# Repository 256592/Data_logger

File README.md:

<!-- Toto je komentář a nebude zobrazen -->

# Univerzální logický analyzátor a data logger
> Semestrální práce

Cílem semestrální práce je návrh a následná realizace hardware univerzálního logického analyzátoru a data loggeru, v rámci bakalářské práce v letním semestru, bude tato práce rozšířena o implementaci firmware a tvorbu uživatelského rozhraní pro PC.

Logický analyzátor je zařízení určené pro sledování a následnou analýzu průběhu
krátkodobých diskrétních signálů, data logger naopak slouží k dlouhodobému záznamu jak digitálních, tak i analogových dat a signálů.

Jako řídící jednotka celého systému je použit mikrokontrolér NXP s jádrem ARM Cortex-M3, 12bitovým A/D převodníkem a zařízením USB 2.0 použitého pro komunikaci s PC. Pro generování časové značky jednotlivých záznamů slouží interní hodiny reálného času s externím krystalem. Součástí zařízení je i možnost připojení externího 24bitového A/D převodníku HX711. Pro uložení zaznamenaných dat je k dispozici SD karta bez filesystemu.

Kanály pro logický analyzátor a data logger jsou oddělené. Logický analyzátor má k dispozici osm kanálů, data logger je 4kanálový. Podpora 5\,V logiky na digitálních vstupech je prozatím zajištěna externě pomocí modulu převodníku napěťových úrovní.

Zařízení je možno napájet z USB, nebo lithium-iontového akumulátoru. Automatické přepínání napájení zajišťuje integrovaný obvod LM66200. Součástí napájecí části je i nabíjecí obvod s ochranou proti přebití, podvybití nebo zkratu akumulátoru.

## HARDWARE

Zařízení se skládá z řídící jednotky, ke které jsou připojeny kanály pro logický analyzátor a data logger, externí paměť ve formě SD karty a externí A/D převodník. Dále jsou k řídící jednotce připojeny uživatelská LED dioda určena pro zpětnou vazbu uživateli a tlačítka ve formě uživatelského tlačítka a tlačítka připojeného na Wakeup pin mikrokontroléru. Zpětnou vazbu při napájení zařízení a nabíjení akumulátoru poskytují další dvě LED diody. Nabíjení akumulátoru zajišťuje nabíjecí obvod popsaný níže. Napájení celého zařízení probíhá buťo pomocí akumulátoru, nebo přes USB-C. Přepínání zdrojů zajišťuje automatický přepínač napájení, ke snížení napájecího napětí na správnou úroveň pak slouží stabilizátor.

<div align="center">
    
    <br>
    <em>Blokový diagram</em>
</div>

## FIRMWARE

Tato část bude náplní především letního semestru, ale již teď je implementovám testovací firmware, který umí komunikovat s aplikací na PC pomocí USB a číst analogové hodnoty z jednoho vstupního kanálu data loggeru. Firmware je psaný v jazyce C, ve vývojovém prostředí MCUXpresso IDE, jako programátor a debugger je použit programátor SEGGER JLink.
Základem testovacího firmware jsou vzorové příklady projektu HID poskytnuté výrobcem mikrokontroléru NXP, do kterého je doplněna obsluha A/D převodníku a rozhodovací logika. Zpráva posílána do PC zatím obsahuje pouze hodnotu, kterou vrací A/D převodník.

<div align="center">
    
    <br>
    <em>Programování a debugging desky</em>
</div>

## SOFTWARE

Tato sekce je věnována návrhu aplikace a grafického prostředí pro konfiguraci, komunikaci s fyzickým zařízením a zpracování dat, která bude také řešena především v letním semestru.
Uživatelské rozhraní bude rozděleno do dvou částí - pro funkci logického analyzátoru a data loggeru. Rozhraní logického analyzátoru bude obsahovat grafické zobrazení zachycené komunikace, možnost analýzy častých komunikačních protokolů (sériová, SPI, I2C komunikace a další). Prostředí data loggeru bude podporovat export dat do formátu CSV, dále bude obsahovat funkce hledání maxima/minima, počítání aritmetického průměru a další funkce.
Aplikace pro obsluhu zařízení je psána v jazyce python v prostředí PyCharm, které dovoluje výběr interpreteru a knihoven přímo ze složky projektu. Díky tomu nedochází ke kolizím s verzemi knhoven nebo samotného pythonu. Pro tvorbu grafického rozhraní je použita knihovna PyQt5, komunikace se zařízením je řešena pomocí knihovny HID a k zápisu zaznamenaných dat do CSV souboru je použita knihovna CSV. 

Zatím je vytvořeno testovací uživatelské rozhraní, ve kterém je implementována funkce zaznamenávání analogových hodnot v reálném čase a to buďto v nastavených časových intervalech a nebo po stisknutí tlačítka. Zaznamenaná data jsou ukládána do souboru CSV a načtena a zobrazována v uživatelském rozhraní. V letním semestru bude aplikace rozšířena o funkci konfigurace zařízení pro funkci data loggeru bez nutnosti připojení k PC během zaznamenávání dat a uživatelské prostředí pro obsluhu logického analyzátoru. Dále budou do aplikace doplněny další funkce pro obsluhu data loggeru, jako například zaznamenávání digitálních hodnot, nebo nástroje pro analýzu dat a zpracování dat.

<div align="center">

    <br>
    <em>Uživatelské rozhraní pro automatické (vlevo) a manuální (vpravo) zaznamenávání dat</em>
</div>

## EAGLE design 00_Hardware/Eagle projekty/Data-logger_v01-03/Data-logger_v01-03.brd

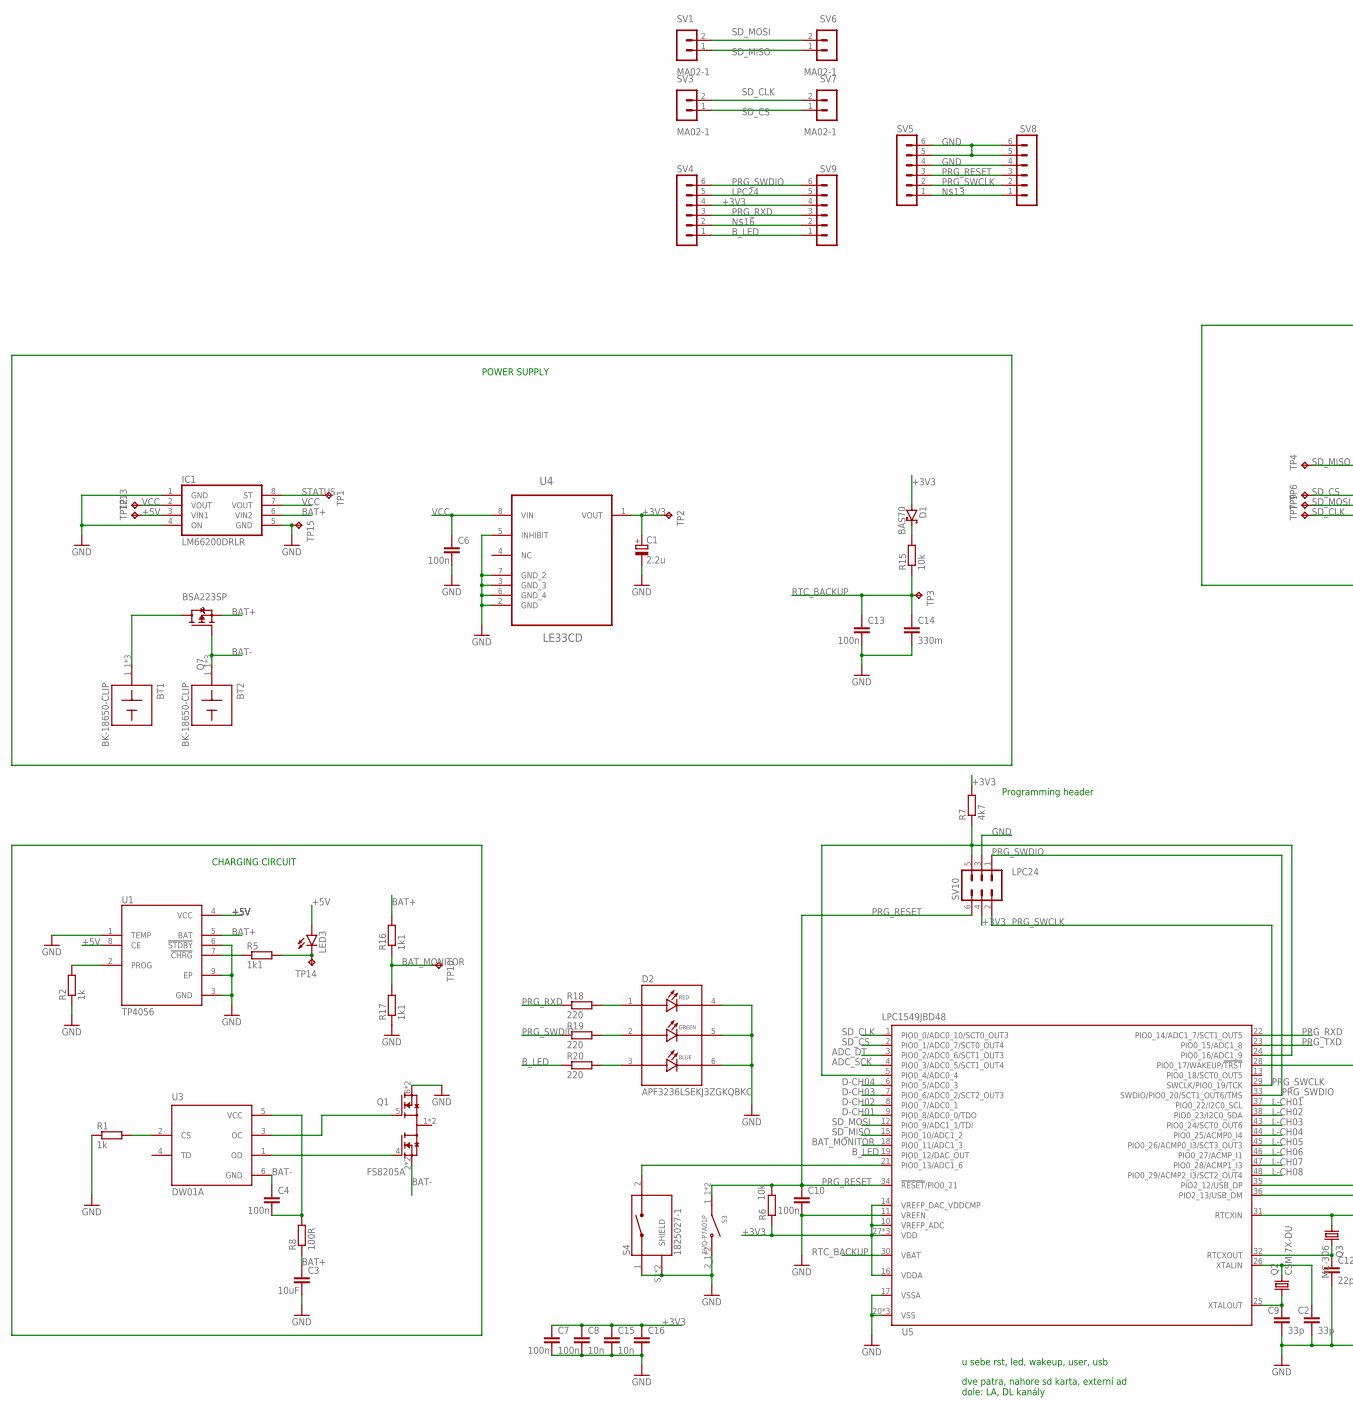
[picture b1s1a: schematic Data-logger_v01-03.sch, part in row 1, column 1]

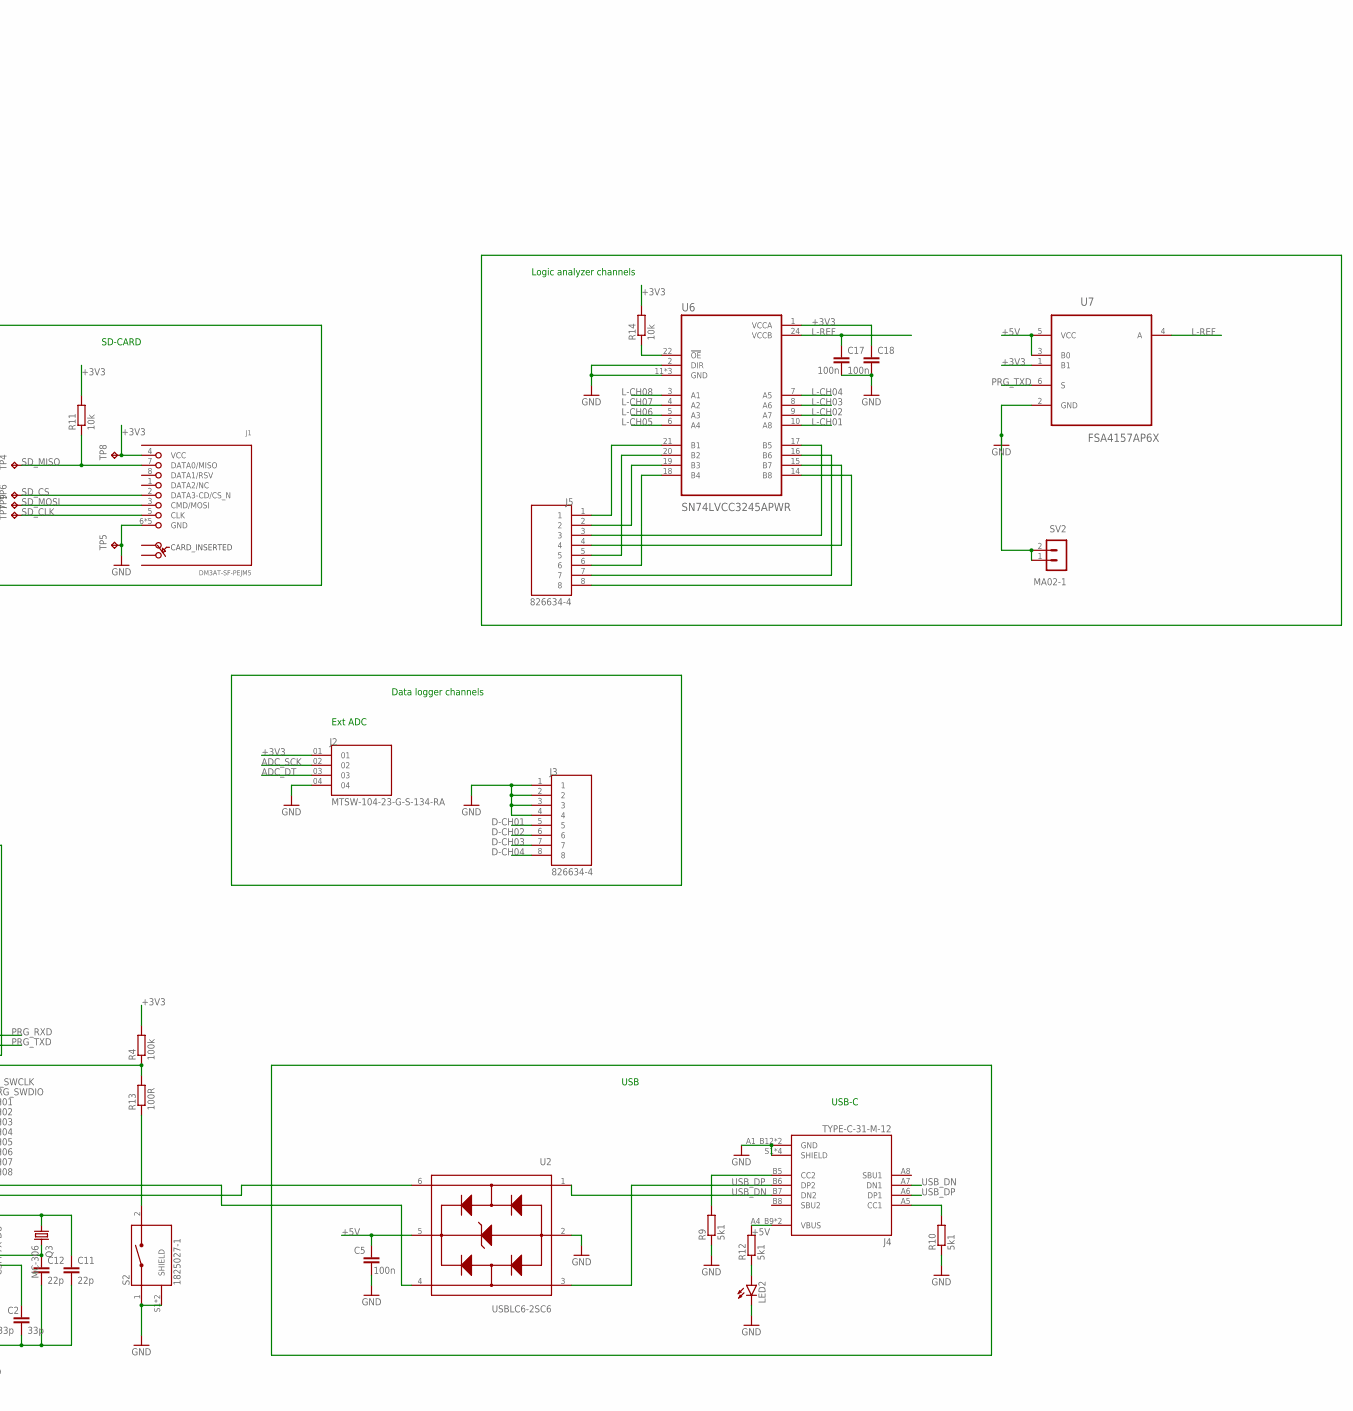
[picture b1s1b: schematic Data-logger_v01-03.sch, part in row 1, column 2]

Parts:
BT1, BT2: BK-18650-CLIP; BAT_BK-18650-CLIP
C1: 2.2u; 140CLH-0810
C2, C9: 33p; C0805
C3: 10uF; C0805
C4, C5, C6, C7, C8, C10, C13, C17, C18: 100n; C0805
C11, C12: 22p; C0805
C14: 330m; C050-050X075
C15, C16: 10n; C0805
D1: BAS70; SOT23
D2: APF3236LSEKJ3ZGKQBKC; LED_APF3236LSEKJ3ZGKQBKC
IC1: LM66200DRLR; SOT8
J1: DM3AT-SF-PEJM5
J2: MTSW-104-23-G-S-134-RA; SAMTEC_MTSW-104-23-G-S-134-RA
J3, J5: 826634-4; TE_826634-4
J4: TYPE-C-31-M-12; HRO_TYPE-C-31-M-12
LED2, LED3: LEDCHIPLED_1206; CHIPLED_1206
Q1: FS8205A; SOP65P640X120-8N
Q2: CSM-7X-DU
Q3: MC-306
Q7: BSA223SP; SC75_INFINEON
R1, R2: 1k; R0805
R4: 100k; R0805
R5, R16, R17: 1k1; R0805
R6, R11, R14, R15: 10k; R0805
R7: 4k7; R0805
R8, R13: 100R; R0805
R9, R10, R12: 5k1; R0805
R18, R19, R20: 220; R0805
S2, S4: 1825027-1; SW_1825027-1
S3: EVQ-P7A01P; SW_EVQ-P7A01P
SV1, SV2, SV3, SV6, SV7: MA02-1
SV4, SV5, SV8, SV9: MA06-1
SV10: MA03-2
TP1, TP2, TP3, TP4, TP5, TP6, TP7, TP8, TP9, TP10, TP12, TP13, TP14, TP15: TPB1,27; B1,27
U1: TP4056; SOP127P600X175-9N
U2: USBLC6-2SC6; SOT95P280X145-6N
U3: DW01A; SOT95P280X145-6N
U4: LE33CD; SOIC127P600X175-8N
U5: LPC1549JBD48; SOT313-2
U6: SN74LVCC3245APWR; SOP65P640X120-24N
U7: FSA4157AP6X; SOT65P210X110-6N

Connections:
+3V3: C1.+, C7.1, C8.1, C15.1, C16.1, C18.1, D1.1 (A), J1.4 (VCC), J2.01, R4.2, R6.1, R7.2, R11.2, R14.2, SV4.4, SV9.4, SV10.4, TP2.TP, TP8.TP, U4.1 (VOUT), U5.10 (VREFP_ADC), U5.14 (VREFP_DAC_VDDCMP), U5.16 (VDDA), U5.27 (VDD), U5.39 (VDD), U5.42 (VDD), U6.1 (VCCA), U7.1 (B1)
+5V: C5.1, IC1.3 (VIN1), J4.A4_B9 (VBUS), J4.B4_A9 (VBUS), LED3.A, R12.2, TP12.TP, U1.4 (VCC), U1.8 (CE), U2.5 (VBUS), U7.3 (B0), U7.5 (VCC)
ADC_DT: J2.03, U5.3 (PIO0_2/ADC0_6/SCT1_OUT3)
ADC_SCK: J2.02, U5.4 (PIO0_3/ADC0_5/SCT1_OUT4)
BAT+: C3.1, IC1.6 (VIN2), Q7.3 (S), R8.1, R16.2, U1.5 (BAT)
BAT-: BT2.1_1, BT2.1_2, BT2.1_3, C4.1, Q1.2 (S1), Q1.3 (S1), Q7.1 (G), U3.6 (GND)
BAT_MONITOR: R16.1, R17.2, TP10.TP, U5.18 (PIO0_11/ADC1_3)
B_LED: R20.1, SV4.1, SV9.1, U5.19 (PIO0_12/DAC_OUT)
D-CH01: J3.5, U5.9 (PIO0_8/ADC0_0/TDO)
D-CH02: J3.6, U5.8 (PIO0_7/ADC0_1)
D-CH03: J3.7, U5.7 (PIO0_6/ADC0_2/SCT2_OUT3)
D-CH04: J3.8, U5.6 (PIO0_5/ADC0_3)
GND: C1.-, C2.2, C3.2, C5.2, C6.2, C7.2, C8.2, C9.2, C10.2, C11.2, C12.2, C13.2, C14.2, C15.2, C16.2, C17.2, C18.2, D2.4 (R_C), D2.5 (G_C), D2.6 (B_C), IC1.1 (GND), IC1.4 (ON), IC1.5 (GND), J1.6 (GND), J1.MOUNT0 (GND), J1.MOUNT1 (GND), J1.MOUNT2 (GND), J1.MOUNT3 (GND), J2.04, J3.1, J3.2, J3.3, J3.4, J4.A1_B12 (GND), J4.B1_A12 (GND), J4.S1 (SHIELD), J4.S2 (SHIELD), J4.S3 (SHIELD), J4.S4 (SHIELD), LED2.C, Q1.6 (S2), Q1.7 (S2), R1.1, R2.1, R9.1, R10.1, R17.1, S2.1, S2.S1 (SHIELD), S2.S2 (SHIELD), S3.2_1 (2), S3.2_2 (2), S4.1, S4.S1 (SHIELD), S4.S2 (SHIELD), SV2.1 (2), SV2.2 (3), SV5.4, SV5.5, SV5.6, SV8.4, SV8.5, SV8.6, SV10.3, TP5.TP, TP15.TP, U1.1 (TEMP), U1.3 (GND), U1.6 (!STDBY), U1.9 (EP), U2.2 (GND), U4.2 (GND), U4.3 (GND_3), U4.5 (INHIBIT), U4.6 (GND_4), U4.7 (GND_2), U5.11 (VREFN), U5.17 (VSSA), U5.20 (VSS), U5.40 (VSS), U5.41 (VSS), U6.2 (DIR), U6.11 (GND), U6.12 (GND), U6.13 (GND), U7.2 (GND)
L-CH01: U5.37 (PIO0_22/I2C0_SCL), U6.10 (A8)
L-CH02: U5.38 (PIO0_23/I2C0_SDA), U6.9 (A7)
L-CH03: U5.43 (PIO0_24/SCT0_OUT6), U6.8 (A6)
L-CH04: U5.44 (PIO0_25/ACMP0_I4), U6.7 (A5)
L-CH05: U5.45 (PIO0_26/ACMP0_I3/SCT3_OUT3), U6.6 (A4)
L-CH06: U5.46 (PIO0_27/ACMP_I1), U6.5 (A3)
L-CH07: U5.47 (PIO0_28/ACMP1_I3), U6.4 (A2)
L-CH08: U5.48 (PIO0_29/ACMP2_I3/SCT2_OUT4), U6.3 (A1)
L-REF: C17.1, U6.24 (VCCB), U7.4 (A)
LPC24: R7.1, SV4.5, SV9.5, SV10.5, U5.5 (PIO0_4/ADC0_4), U5.24 (PIO0_16/ADC1_9)
LPC25: C9.1, Q2.1, U5.25 (XTALOUT)
LPC26: C2.1, Q2.2, U5.26 (XTALIN)
LPC31: C11.1, Q3.1, U5.31 (RTCXIN)
LPC32: C12.1, Q3.4 (2), U5.32 (RTCXOUT)
LPC_DM: U2.4 (I/O2_OUT), U5.35 (PIO2_12/USB_DP)
unnamed: R2.2, U1.2 (PROG)
unnamed: C4.2, R8.2, U3.5 (VCC)
unnamed: R1.2, U3.2 (CS)
unnamed: Q1.4 (G1), U3.1 (OD)
unnamed: Q1.5 (G2), U3.3 (OC)
unnamed: R5.1, U1.7 (!CHRG)
unnamed: J4.A5 (CC1), R10.2
unnamed: LED3.C, R5.2, TP14.TP
unnamed: R4.1, R13.2, SV5.1, SV8.1, U5.28 (PIO0_17/WAKEUP/!TRST)
unnamed: R13.1, S2.2
unnamed: J4.B5 (CC2), R9.2
unnamed: S4.2, SV4.2, SV9.2, U5.21 (PIO0_13/ADC1_6)
unnamed: LED2.A, R12.1
unnamed: J5.1, U6.21 (B1)
unnamed: J5.5, U6.20 (B2)
unnamed: D2.1 (R_A), R18.2
unnamed: D1.3 (C), R15.2
unnamed: D2.2 (G_A), R19.2
unnamed: D2.3 (B_A), R20.2
unnamed: J5.2, U6.19 (B3)
unnamed: BT1.1_1, BT1.1_2, BT1.1_3, Q7.2 (D)
unnamed: J5.6, U6.18 (B4)
unnamed: J5.3, U6.17 (B5)
unnamed: J5.7, U6.16 (B6)
unnamed: J5.8, U6.14 (B8)
unnamed: J5.4, U6.15 (B7)
unnamed: U2.6 (I/O1_OUT), U5.36 (PIO2_13/USB_DM)
unnamed: R14.1, U6.22 (!OE)
PRG_RESET: C10.1, R6.2, S3.1_1 (1), S3.1_2 (1), SV5.3, SV8.3, SV10.6, U5.34 (!RESET!/PIO0_21)
PRG_RXD: R18.1, SV4.3, SV9.3, U5.22 (PIO0_14/ADC1_7/SCT1_OUT5)
PRG_SWCLK: SV5.2, SV8.2, SV10.2, U5.29 (SWCLK/PIO0_19/TCK)
PRG_SWDIO: R19.1, SV4.6, SV9.6, SV10.1, U5.33 (SWDIO/PIO0_20/SCT1_OUT6/TMS)
PRG_TXD: U5.23 (PIO0_15/ADC1_8), U7.6 (S)
RTC_BACKUP: C13.1, C14.1, R15.1, TP3.TP, U5.30 (VBAT)
SD_CLK: J1.5 (CLK), SV3.2 (3), SV7.2 (3), TP7.TP, U5.1 (PIO0_0/ADC0_10/SCT0_OUT3)
SD_CS: J1.2 (DATA3-CD/CS_N), SV3.1 (2), SV7.1 (2), TP6.TP, U5.2 (PIO0_1/ADC0_7/SCT0_OUT4)
SD_MISO: J1.7 (DATA0/MISO), R11.1, SV1.1 (2), SV6.1 (2), TP4.TP, U5.15 (PIO0_10/ADC1_2)
SD_MOSI: J1.3 (CMD/MOSI), SV1.2 (3), SV6.2 (3), TP9.TP, U5.12 (PIO0_9/ADC1_1/TDI)
STATUS: IC1.8 (ST), TP1.TP
USB_DN: J4.A7 (DN1), J4.B7 (DN2), U2.1 (I/O1_IN)
USB_DP: J4.A6 (DP1), J4.B6 (DP2), U2.3 (I/O2_IN)
VCC: C6.1, IC1.2 (VOUT), IC1.7 (VOUT), TP13.TP, U4.8 (VIN)

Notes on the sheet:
USB-C
SD-CARD
POWER SUPPLY
CHARGING CIRCUIT
Programming header
Logic analyzer channels
Data logger channels
Ext ADC
USB
u sebe rst, led, wakeup, user, usb
dve patra, nahore sd karta, externí ad dole: LA, DL kanály

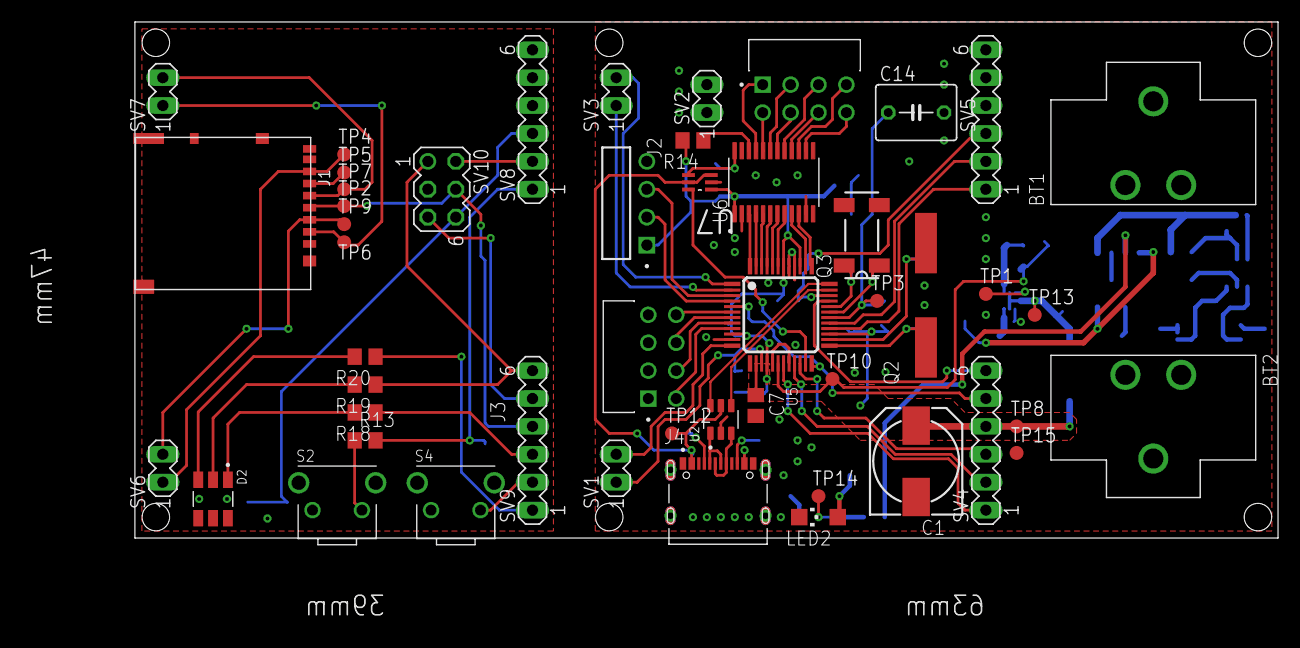
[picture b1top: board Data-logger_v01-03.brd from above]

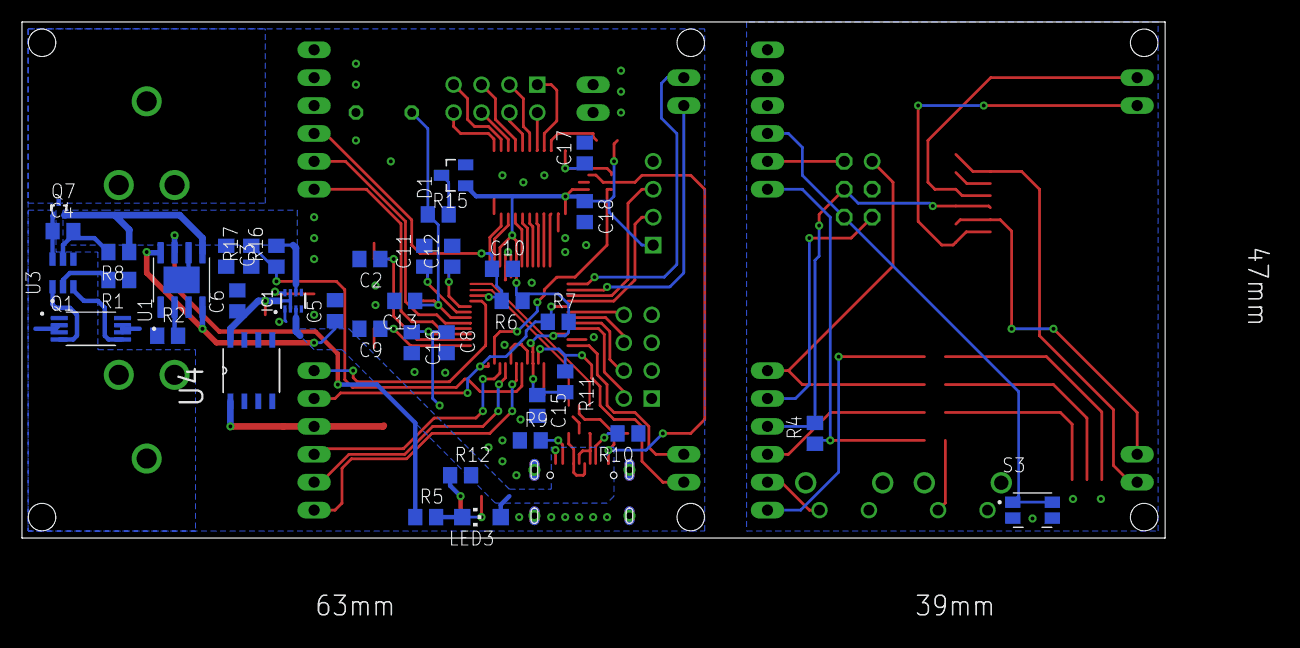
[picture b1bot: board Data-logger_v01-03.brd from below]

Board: 2 copper layers, 104.1 x 47.0 mm, 87 parts (38 on the bottom side), 70 nets.

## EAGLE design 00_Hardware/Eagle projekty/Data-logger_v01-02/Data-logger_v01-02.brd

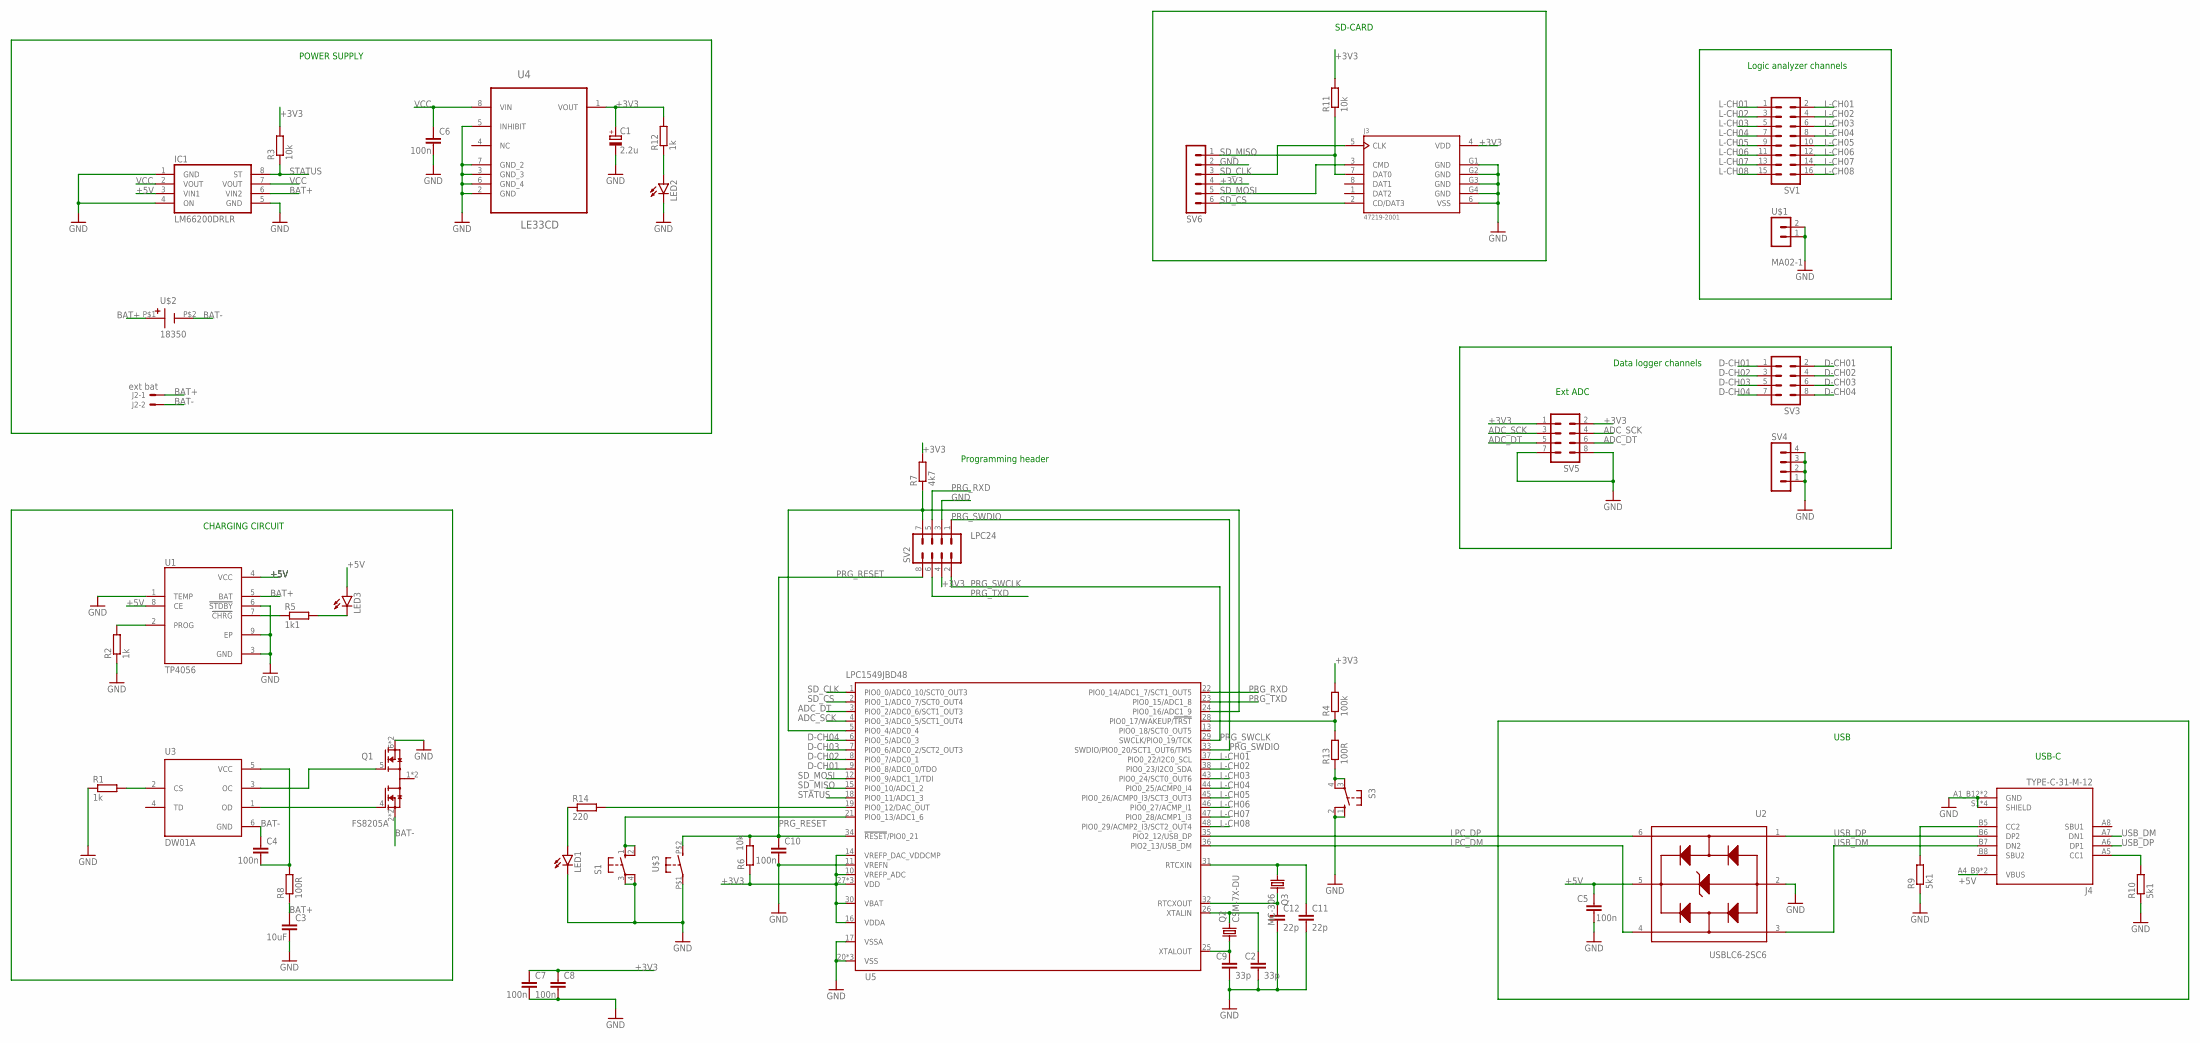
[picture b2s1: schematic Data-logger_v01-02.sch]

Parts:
C1: 2.2u; 140CLH-0810
C2, C9: 33p; C0805
C3: 10uF; C0805
C4, C5, C6, C7, C8, C10: 100n; C0805
C11, C12: 22p; C0805
IC1: LM66200DRLR; SOT8
J2: ext bat; 7395-02
J3: 47219-2001; MOLEX_47219-2001
J4: TYPE-C-31-M-12; HRO_TYPE-C-31-M-12
LED1, LED2, LED3: LEDCHIPLED_1206; CHIPLED_1206
Q1: FS8205A; SOP65P640X120-8N
Q2: CSM-7X-DU
Q3: MC-306
R1, R2, R12: 1k; R0805
R3, R6, R11: 10k; R0805
R4: 100k; R0805
R5: 1k1; R0805
R7: 4k7; R0805
R8, R13: 100R; R0805
R9, R10: 5k1; R0805
R14: 220; R0805
S1, S3: 10-XX; B3F-10XX
SV1: MA08-2
SV2, SV3, SV5: MA04-2
SV4: MA04-1
SV6: MA06-1
U1: TP4056; SOP127P600X175-9N
U2: USBLC6-2SC6; SOT95P280X145-6N
U3: DW01A; SOT95P280X145-6N
U4: LE33CD; SOIC127P600X175-8N
U5: LPC1549JBD48; SOT313-2
U$1: MA02-1
U$2: 18350
U$3: BUTTON_SMD_MINI; PTS636SP43SMTRLFS

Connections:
+3V3: C1.+, C7.1, C8.1, J3.4 (VDD), R3.2, R4.2, R6.1, R7.2, R11.2, R12.2, SV2.4, SV5.1, SV5.2, SV6.4, U4.1 (VOUT), U5.10 (VREFP_ADC), U5.14 (VREFP_DAC_VDDCMP), U5.16 (VDDA), U5.27 (VDD), U5.30 (VBAT), U5.39 (VDD), U5.42 (VDD)
+5V: C5.1, IC1.3 (VIN1), J4.A4_B9 (VBUS), J4.B4_A9 (VBUS), LED3.A, U1.4 (VCC), U1.8 (CE), U2.5 (VBUS)
ADC_DT: SV5.5, SV5.6, U5.3 (PIO0_2/ADC0_6/SCT1_OUT3)
ADC_SCK: SV5.3, SV5.4, U5.4 (PIO0_3/ADC0_5/SCT1_OUT4)
BAT+: C3.1, IC1.6 (VIN2), J2.1, R8.1, U1.5 (BAT), U$2.P$1 (+)
BAT-: C4.1, J2.2, Q1.2 (S1), Q1.3 (S1), U3.6 (GND), U$2.P$2 (-)
D-CH01: SV3.1, SV3.2, U5.9 (PIO0_8/ADC0_0/TDO)
D-CH02: SV3.3, SV3.4, U5.8 (PIO0_7/ADC0_1)
D-CH03: SV3.5, SV3.6, U5.7 (PIO0_6/ADC0_2/SCT2_OUT3)
D-CH04: SV3.7, SV3.8, U5.6 (PIO0_5/ADC0_3)
GND: C1.-, C2.2, C3.2, C5.2, C6.2, C7.2, C8.2, C9.2, C10.2, C11.2, C12.2, IC1.1 (GND), IC1.4 (ON), IC1.5 (GND), J3.6 (VSS), J3.G1 (GND), J3.G2 (GND), J3.G3 (GND), J3.G4 (GND), J4.A1_B12 (GND), J4.B1_A12 (GND), J4.S1 (SHIELD), J4.S2 (SHIELD), J4.S3 (SHIELD), J4.S4 (SHIELD), LED1.C, LED2.C, Q1.6 (S2), Q1.7 (S2), R1.1, R2.1, R9.1, R10.1, S1.3, S1.4 (P1), S3.1 (S), S3.2 (S1), SV2.3, SV4.1, SV4.2, SV4.3, SV4.4, SV5.7, SV5.8, SV6.2, U1.1 (TEMP), U1.3 (GND), U1.6 (!STDBY), U1.9 (EP), U2.2 (GND), U4.2 (GND), U4.3 (GND_3), U4.5 (INHIBIT), U4.6 (GND_4), U4.7 (GND_2), U5.11 (VREFN), U5.17 (VSSA), U5.20 (VSS), U5.40 (VSS), U5.41 (VSS), U$1.1 (2), U$1.2 (3), U$3.P$1
L-CH01: SV1.1, SV1.2, U5.37 (PIO0_22/I2C0_SCL)
L-CH02: SV1.3, SV1.4, U5.38 (PIO0_23/I2C0_SDA)
L-CH03: SV1.5, SV1.6, U5.43 (PIO0_24/SCT0_OUT6)
L-CH04: SV1.7, SV1.8, U5.44 (PIO0_25/ACMP0_I4)
L-CH05: SV1.9, SV1.10, U5.45 (PIO0_26/ACMP0_I3/SCT3_OUT3)
L-CH06: SV1.11, SV1.12, U5.46 (PIO0_27/ACMP_I1)
L-CH07: SV1.13, SV1.14, U5.47 (PIO0_28/ACMP1_I3)
L-CH08: SV1.15, SV1.16, U5.48 (PIO0_29/ACMP2_I3/SCT2_OUT4)
LPC24: R7.1, SV2.7, U5.5 (PIO0_4/ADC0_4), U5.24 (PIO0_16/ADC1_9)
LPC25: C9.1, Q2.1, U5.25 (XTALOUT)
LPC26: C2.1, Q2.2, U5.26 (XTALIN)
LPC31: C11.1, Q3.1, U5.31 (RTCXIN)
LPC32: C12.1, Q3.4 (2), U5.32 (RTCXOUT)
LPC_DM: U2.4 (I/O2_OUT), U5.36 (PIO2_13/USB_DM)
LPC_DP: U2.6 (I/O1_OUT), U5.35 (PIO2_12/USB_DP)
unnamed: R2.2, U1.2 (PROG)
unnamed: C4.2, R8.2, U3.5 (VCC)
unnamed: R1.2, U3.2 (CS)
unnamed: Q1.4 (G1), U3.1 (OD)
unnamed: Q1.5 (G2), U3.3 (OC)
unnamed: R5.1, U1.7 (!CHRG)
unnamed: J4.A5 (CC1), R10.2
unnamed: LED3.C, R5.2
unnamed: R4.1, R13.2, U5.28 (PIO0_17/WAKEUP/!TRST)
unnamed: R13.1, S3.3, S3.4 (P1)
unnamed: J4.B5 (CC2), R9.2
unnamed: S1.1 (S), S1.2 (S1), U5.21 (PIO0_13/ADC1_6)
unnamed: LED2.A, R12.1
unnamed: LED1.A, R14.1
unnamed: R14.2, U5.19 (PIO0_12/DAC_OUT)
PRG_RESET: C10.1, R6.2, SV2.8, U5.34 (!RESET!/PIO0_21), U$3.P$2 (S)
PRG_RXD: SV2.5, U5.22 (PIO0_14/ADC1_7/SCT1_OUT5)
PRG_SWCLK: SV2.2, U5.29 (SWCLK/PIO0_19/TCK)
PRG_SWDIO: SV2.1, U5.33 (SWDIO/PIO0_20/SCT1_OUT6/TMS)
PRG_TXD: SV2.6, U5.23 (PIO0_15/ADC1_8)
SD_CLK: J3.5 (CLK), SV6.3, U5.1 (PIO0_0/ADC0_10/SCT0_OUT3)
SD_CS: J3.2 (CD/DAT3), SV6.6, U5.2 (PIO0_1/ADC0_7/SCT0_OUT4)
SD_MISO: J3.7 (DAT0), R11.1, SV6.1, U5.15 (PIO0_10/ADC1_2)
SD_MOSI: J3.3 (CMD), SV6.5, U5.12 (PIO0_9/ADC1_1/TDI)
STATUS: IC1.8 (ST), R3.1, U5.18 (PIO0_11/ADC1_3)
USB_DM: J4.A7 (DN1), J4.B7 (DN2), U2.3 (I/O2_IN)
USB_DP: J4.A6 (DP1), J4.B6 (DP2), U2.1 (I/O1_IN)
VCC: C6.1, IC1.2 (VOUT), IC1.7 (VOUT), U4.8 (VIN)

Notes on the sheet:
USB-C
SD-CARD
POWER SUPPLY
CHARGING CIRCUIT
Programming header
Logic analyzer channels
Data logger channels
Ext ADC
USB

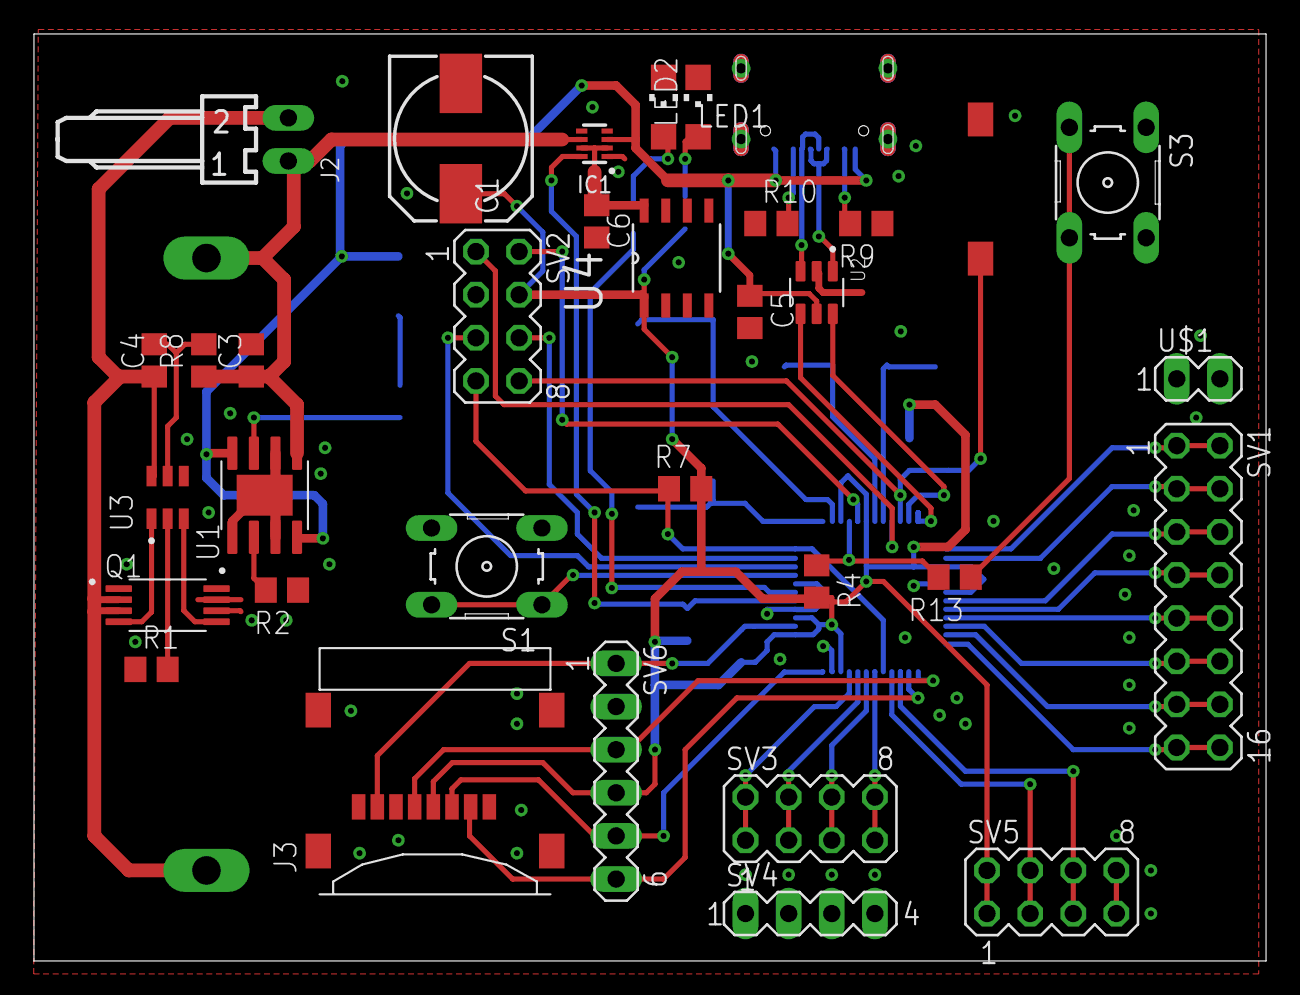
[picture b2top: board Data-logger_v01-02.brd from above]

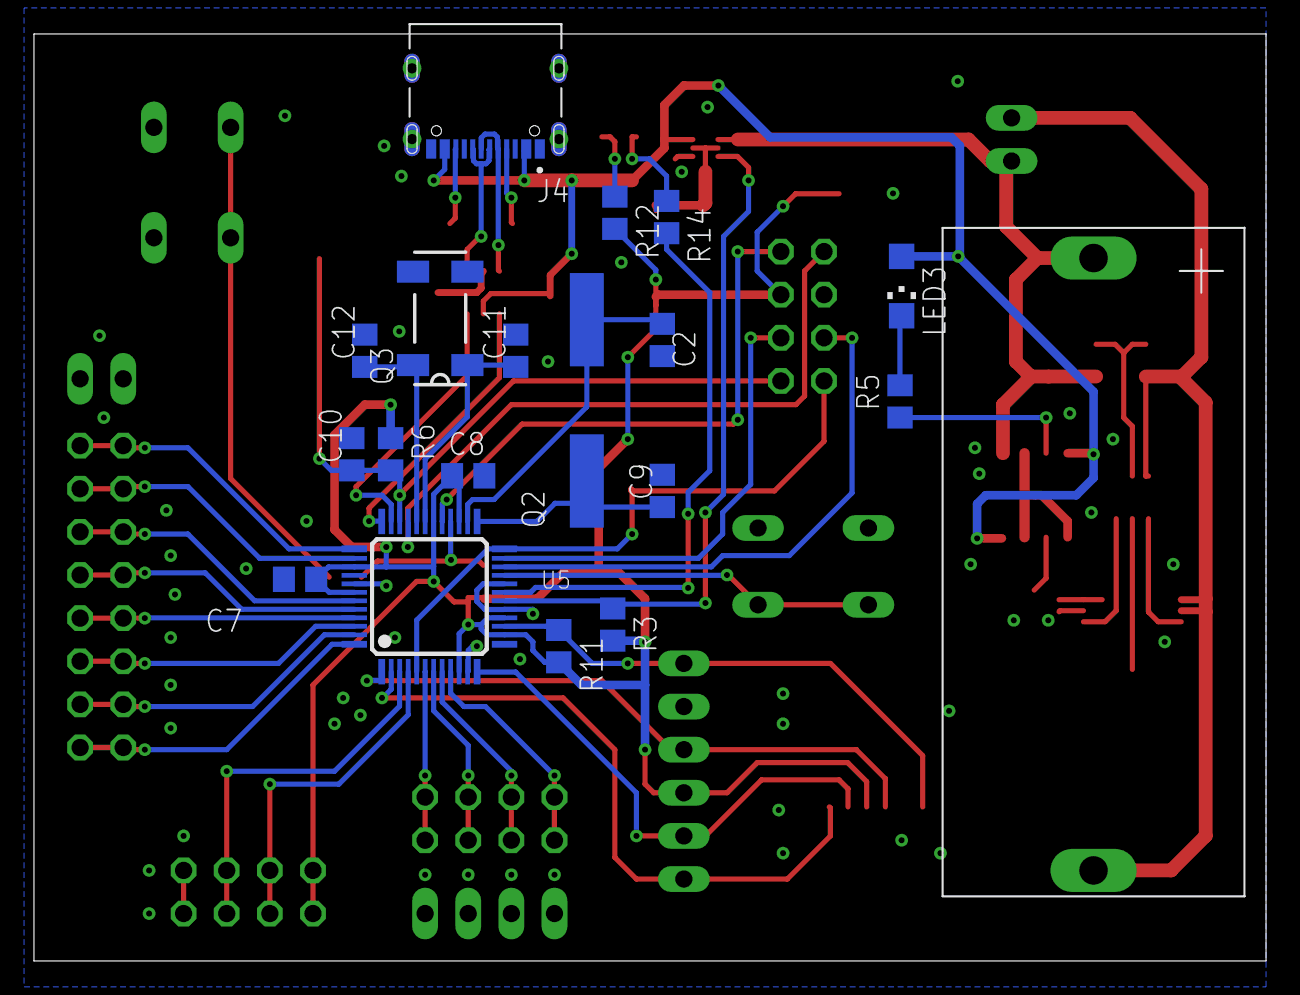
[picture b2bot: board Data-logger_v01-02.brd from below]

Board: 2 copper layers, 72.6 x 54.6 mm, 52 parts (19 on the bottom side), 54 nets.

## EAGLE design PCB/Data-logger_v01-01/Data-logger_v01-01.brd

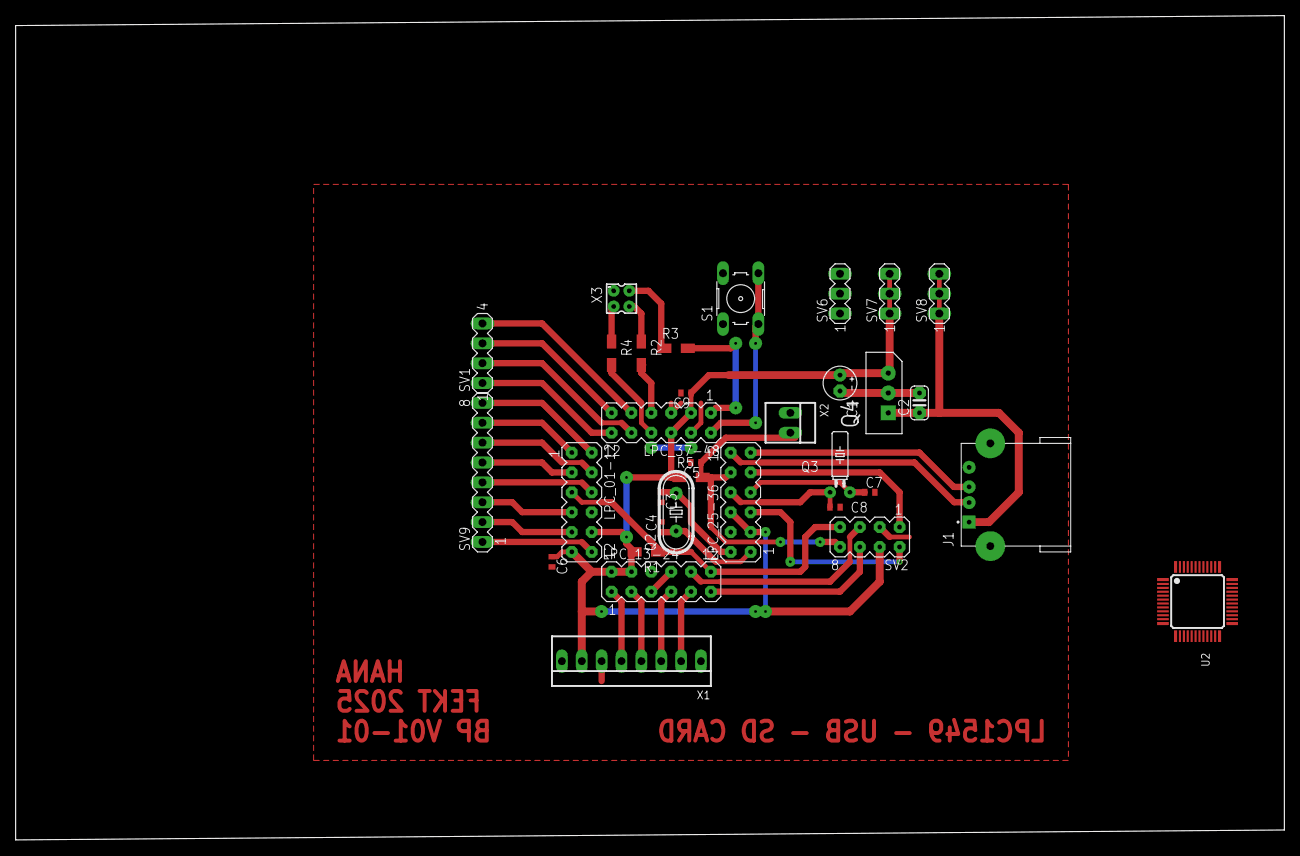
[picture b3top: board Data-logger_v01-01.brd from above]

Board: 2 copper layers, 162.2 x 105.4 mm, 33 parts (0 on the bottom side), 41 nets.

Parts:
C1: 2.2u; E2-4
C2: 100n; C025-024X044
C3, C4: 33p; C0402
C5, C6, C9: 100n; C0402
C7, C8: 22p; C0402
J1: 6364372-1; TE_6364372-1
LPC_01-12, LPC_13-24, LPC_25-36, LPC_37-48: MA06-2
Q2: HC49/S
Q3: TC26H
Q4: LF33CV; TO254P450X1020X1935-3P
R1: 4k7; R1206W
R2, R4: 1k1; R1206W
R3: 300R; R1206W
R5: 10k; R1206W
S1: B3F-10XX
SV1: MA04-1
SV2: MA04-2
SV6, SV7, SV8: MA03-1
SV9: MA08-1
U2: LPC1549JBD48; SOT313-2
X1: 22-23-2081
X2: 22-23-2021
X3: 87758-0416

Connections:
+3V3: C1.+, C6.1, C9.1, LPC_01-12.10, LPC_01-12.11, LPC_13-24.2, LPC_13-24.4, LPC_25-36.3, LPC_25-36.6, LPC_37-48.3, LPC_37-48.6, Q4.3, R1.2, R5.1, SV2.4, SV7.1, SV7.2, SV7.3, U2.10, U2.11, U2.14, U2.16, U2.27, U2.30, U2.39, U2.42, X1.7
+5V: C2.1, J1.1, Q4.1, SV8.1, SV8.2, SV8.3
CS: LPC_13-24.1, U2.13, X1.5
GND: C1.-, C2.2, C3.2, C4.2, C5.2, C6.2, C7.2, C8.2, C9.2, J1.4, J1.S1, J1.S2, LPC_13-24.5, LPC_13-24.8, LPC_37-48.4, LPC_37-48.5, Q4.2, S1.1, S1.2, SV2.3, SV6.1, SV6.2, SV6.3, U2.17, U2.20, U2.40, U2.41, X1.1, X1.6, X1.8, X2.1, X3.1
LPC01: LPC_01-12.1, SV9.7, U2.1
LPC02: LPC_01-12.2, SV9.8, U2.2
LPC03: LPC_01-12.3, SV9.5, U2.3
LPC04: LPC_01-12.4, SV9.6, U2.4
LPC06: LPC_01-12.6, SV9.4, U2.6
LPC07: LPC_01-12.7, SV9.3, U2.7
LPC08: LPC_01-12.8, U2.8
LPC09: LPC_01-12.9, SV9.2, U2.9
LPC12: LPC_01-12.12, SV9.1, U2.12
LPC18: LPC_13-24.6, U2.18
LPC24: LPC_01-12.5, LPC_13-24.12, R1.1, SV2.7, U2.5, U2.24
LPC25: C4.1, LPC_25-36.1, Q2.1, U2.25
LPC26: C3.1, LPC_25-36.2, Q2.2, U2.26
LPC28: LPC_25-36.4, U2.28
LPC31: C7.1, LPC_25-36.7, Q3.2, U2.31
LPC32: C8.1, LPC_25-36.8, Q3.1, U2.32
LPC37: LPC_37-48.1, R3.2, U2.37
LPC38: LPC_37-48.2, S1.3, S1.4, U2.38
LPC43: LPC_37-48.7, R2.2, U2.43
LPC44: LPC_37-48.8, R4.2, U2.44
LPC45: LPC_37-48.9, SV1.4, U2.45
LPC46: LPC_37-48.10, SV1.2, U2.46
LPC47: LPC_37-48.11, SV1.3, U2.47
LPC48: LPC_37-48.12, SV1.1, U2.48
MISO: LPC_13-24.9, U2.21, X1.2
MOSI: LPC_13-24.3, U2.15, X1.4
unnamed: R2.1, X3.4
unnamed: R3.1, X3.2
unnamed: R4.1, X3.3
PRG_RESET: C5.1, LPC_25-36.10, R5.2, SV2.8, U2.34, X2.2
PRG_RXD: LPC_13-24.10, SV2.5, U2.22
PRG_SWCLK: LPC_25-36.5, SV2.2, U2.29
PRG_SWDIO: LPC_25-36.9, SV2.1, U2.33
PRG_TXD: LPC_13-24.11, SV2.6, U2.23
SCK: LPC_13-24.7, U2.19, X1.3
USB_DM: J1.2, LPC_25-36.12, U2.36
USB_DP: J1.3, LPC_25-36.11, U2.35

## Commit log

2025-10-16 upload
2025-10-21 update components values
2026-01-06 upload 3d model
